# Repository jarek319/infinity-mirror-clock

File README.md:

# infinity-mirror-clock
An interesting visualization using the Infinity Mirror effect with a ring of RGB LEDs

I was playing with two-way acrylic and held it over a few Neopixels I had on hand, and found a really cool Infinity Mirror effect occuring when I angled the acrylic just right. Thinking about a good application for this, I decided to use to the effect to create "hands" for an analog-styled clock made of LEDs.

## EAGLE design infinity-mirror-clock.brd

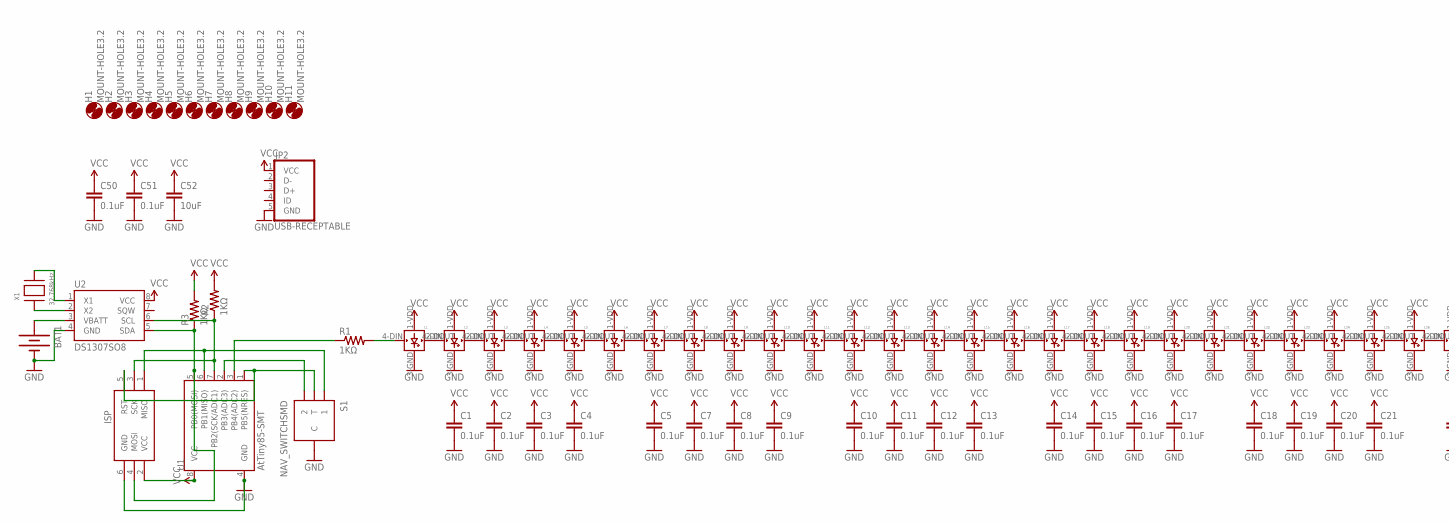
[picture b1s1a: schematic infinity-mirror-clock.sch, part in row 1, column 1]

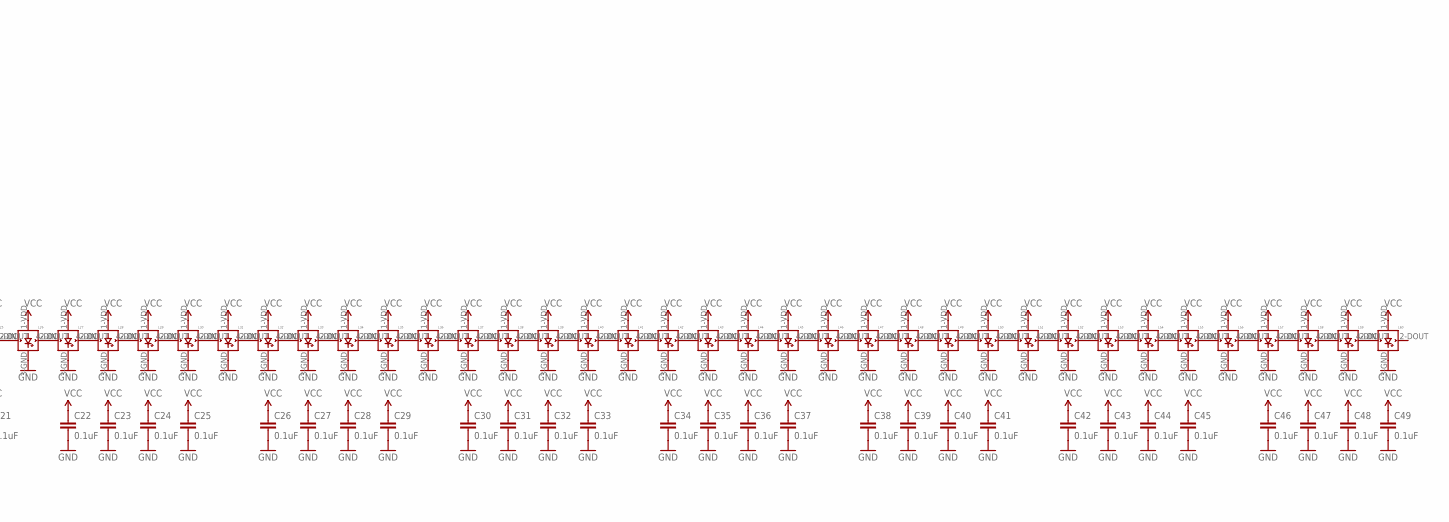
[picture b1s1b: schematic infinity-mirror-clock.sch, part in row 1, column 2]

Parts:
BAT1: BATTERY12MM; BATTCON_12MM
C1, C2, C3, C4, C5, C7, C8, C9, C10, C11, C12, C13, C14, C15, C16, C17, C18, C19, C20, C21, C22, C23, C24, C25, C26, C27, C28, C29, C30, C31, C32, C33, C34, C35, C36, C37, C38, C39, C40, C41, C42, C43, C44, C45, C46, C47, C48, C49, C50, C51: 0.1uF; 0603-CAP
C52: 10uF; 0603-CAP
H1, H2, H3, H4, H5, H6, H7, H8, H9, H10, H11: MOUNT-HOLE3.2; 3,2
ISP: AVRISPAVRSMTISP; AVRSMTISP
JP2: USB-RECEPTABLE; FCI-10103594-0001LF
L1, L2, L3, L4, L5, L6, L7, L8, L9, L10, L11, L12, L13, L14, L15, L16, L17, L18, L19, L20, L21, L22, L23, L24, L25, L26, L27, L28, L29, L30, L31, L32, L33, L34, L35, L36, L37, L38, L39, L40, L41, L42, L43, L44, L45, L46, L47, L48, L49, L50, L51, L52, L53, L54, L55, L56, L57, L58, L59, L60: WS2812B
R1: 1KΩ; 0603-RES
R2, R3: 1KΩ; R0603
S1: NAV_SWITCHSMD; NAV_SWITCH
U1: AtTiny85-SMT; SO08-EIAJ
U2: DS1307SO8; SO08
X1: 32.768kHz; XTAL3215

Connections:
GND: BAT1.GND (-), C1.2, C2.2, C3.2, C4.2, C5.2, C7.2, C8.2, C9.2, C10.2, C11.2, C12.2, C13.2, C14.2, C15.2, C16.2, C17.2, C18.2, C19.2, C20.2, C21.2, C22.2, C23.2, C24.2, C25.2, C26.2, C27.2, C28.2, C29.2, C30.2, C31.2, C32.2, C33.2, C34.2, C35.2, C36.2, C37.2, C38.2, C39.2, C40.2, C41.2, C42.2, C43.2, C44.2, C45.2, C46.2, C47.2, C48.2, C49.2, C50.2, C51.2, C52.2, ISP.6 (GND), JP2.5 (GND), L1.3-GND (GND), L2.3-GND (GND), L3.3-GND (GND), L4.3-GND (GND), L5.3-GND (GND), L6.3-GND (GND), L7.3-GND (GND), L8.3-GND (GND), L9.3-GND (GND), L10.3-GND (GND), L11.3-GND (GND), L12.3-GND (GND), L13.3-GND (GND), L14.3-GND (GND), L15.3-GND (GND), L16.3-GND (GND), L17.3-GND (GND), L18.3-GND (GND), L19.3-GND (GND), L20.3-GND (GND), L21.3-GND (GND), L22.3-GND (GND), L23.3-GND (GND), L24.3-GND (GND), L25.3-GND (GND), L26.3-GND (GND), L27.3-GND (GND), L28.3-GND (GND), L29.3-GND (GND), L30.3-GND (GND), L31.3-GND (GND), L32.3-GND (GND), L33.3-GND (GND), L34.3-GND (GND), L35.3-GND (GND), L36.3-GND (GND), L37.3-GND (GND), L38.3-GND (GND), L39.3-GND (GND), L40.3-GND (GND), L41.3-GND (GND), L42.3-GND (GND), L43.3-GND (GND), L44.3-GND (GND), L45.3-GND (GND), L46.3-GND (GND), L47.3-GND (GND), L48.3-GND (GND), L49.3-GND (GND), L50.3-GND (GND), L51.3-GND (GND), L52.3-GND (GND), L53.3-GND (GND), L54.3-GND (GND), L55.3-GND (GND), L56.3-GND (GND), L57.3-GND (GND), L58.3-GND (GND), L59.3-GND (GND), L60.3-GND (GND), S1.C, U1.4 (GND), U2.4 (GND)
unnamed: L1.2-DOUT (DOUT), L2.4-DIN (DIN)
unnamed: L2.2-DOUT (DOUT), L3.4-DIN (DIN)
unnamed: L3.2-DOUT (DOUT), L4.4-DIN (DIN)
unnamed: L4.2-DOUT (DOUT), L5.4-DIN (DIN)
unnamed: L5.2-DOUT (DOUT), L6.4-DIN (DIN)
unnamed: L7.2-DOUT (DOUT), L8.4-DIN (DIN)
unnamed: L8.2-DOUT (DOUT), L9.4-DIN (DIN)
unnamed: L9.2-DOUT (DOUT), L10.4-DIN (DIN)
unnamed: L10.2-DOUT (DOUT), L11.4-DIN (DIN)
unnamed: L11.2-DOUT (DOUT), L12.4-DIN (DIN)
unnamed: L13.2-DOUT (DOUT), L14.4-DIN (DIN)
unnamed: L14.2-DOUT (DOUT), L15.4-DIN (DIN)
unnamed: L15.2-DOUT (DOUT), L16.4-DIN (DIN)
unnamed: L16.2-DOUT (DOUT), L17.4-DIN (DIN)
unnamed: L17.2-DOUT (DOUT), L18.4-DIN (DIN)
unnamed: L19.2-DOUT (DOUT), L20.4-DIN (DIN)
unnamed: L20.2-DOUT (DOUT), L21.4-DIN (DIN)
unnamed: L21.2-DOUT (DOUT), L22.4-DIN (DIN)
unnamed: L22.2-DOUT (DOUT), L23.4-DIN (DIN)
unnamed: L23.2-DOUT (DOUT), L24.4-DIN (DIN)
unnamed: L25.2-DOUT (DOUT), L26.4-DIN (DIN)
unnamed: L26.2-DOUT (DOUT), L27.4-DIN (DIN)
unnamed: L27.2-DOUT (DOUT), L28.4-DIN (DIN)
unnamed: L28.2-DOUT (DOUT), L29.4-DIN (DIN)
unnamed: L29.2-DOUT (DOUT), L30.4-DIN (DIN)
unnamed: L31.2-DOUT (DOUT), L32.4-DIN (DIN)
unnamed: L32.2-DOUT (DOUT), L33.4-DIN (DIN)
unnamed: L33.2-DOUT (DOUT), L34.4-DIN (DIN)
unnamed: L34.2-DOUT (DOUT), L35.4-DIN (DIN)
unnamed: L35.2-DOUT (DOUT), L36.4-DIN (DIN)
unnamed: L37.2-DOUT (DOUT), L38.4-DIN (DIN)
unnamed: L38.2-DOUT (DOUT), L39.4-DIN (DIN)
unnamed: L39.2-DOUT (DOUT), L40.4-DIN (DIN)
unnamed: L40.2-DOUT (DOUT), L41.4-DIN (DIN)
unnamed: L41.2-DOUT (DOUT), L42.4-DIN (DIN)
unnamed: L43.2-DOUT (DOUT), L44.4-DIN (DIN)
unnamed: L44.2-DOUT (DOUT), L45.4-DIN (DIN)
unnamed: L45.2-DOUT (DOUT), L46.4-DIN (DIN)
unnamed: L46.2-DOUT (DOUT), L47.4-DIN (DIN)
unnamed: L47.2-DOUT (DOUT), L48.4-DIN (DIN)
unnamed: L49.2-DOUT (DOUT), L50.4-DIN (DIN)
unnamed: L50.2-DOUT (DOUT), L51.4-DIN (DIN)
unnamed: L51.2-DOUT (DOUT), L52.4-DIN (DIN)
unnamed: L52.2-DOUT (DOUT), L53.4-DIN (DIN)
unnamed: L53.2-DOUT (DOUT), L54.4-DIN (DIN)
unnamed: L55.2-DOUT (DOUT), L56.4-DIN (DIN)
unnamed: L56.2-DOUT (DOUT), L57.4-DIN (DIN)
unnamed: L57.2-DOUT (DOUT), L58.4-DIN (DIN)
unnamed: L58.2-DOUT (DOUT), L59.4-DIN (DIN)
unnamed: L59.2-DOUT (DOUT), L60.4-DIN (DIN)
unnamed: L1.4-DIN (DIN), R1.2
unnamed: U2.2 (X2), X1.P$1
unnamed: U2.1 (X1), X1.P$2
unnamed: BAT1.PWR@1 (+), U2.3 (VBATT)
unnamed: ISP.3 (SCK), R2.1, U1.7 (PB2(SCK/ADC1)), U2.6 (SCL)
unnamed: ISP.4 (MOSI), R3.1, U1.5 (PB0(MOSI)), U2.5 (SDA)
unnamed: ISP.1 (MISO), S1.1, U1.6 (PB1(MISO))
unnamed: S1.2, U1.2 (PB3(ADC3))
unnamed: ISP.5 (RST), S1.T, U1.1 (PB5(NRES))
unnamed: R1.1, U1.3 (PB4(ADC2))
unnamed: L30.2-DOUT (DOUT), L31.4-DIN (DIN)
unnamed: L24.2-DOUT (DOUT), L25.4-DIN (DIN)
unnamed: L18.2-DOUT (DOUT), L19.4-DIN (DIN)
unnamed: L12.2-DOUT (DOUT), L13.4-DIN (DIN)
unnamed: L36.2-DOUT (DOUT), L37.4-DIN (DIN)
unnamed: L42.2-DOUT (DOUT), L43.4-DIN (DIN)
unnamed: L48.2-DOUT (DOUT), L49.4-DIN (DIN)
unnamed: L54.2-DOUT (DOUT), L55.4-DIN (DIN)
unnamed: L6.2-DOUT (DOUT), L7.4-DIN (DIN)
VCC: C1.1, C2.1, C3.1, C4.1, C5.1, C7.1, C8.1, C9.1, C10.1, C11.1, C12.1, C13.1, C14.1, C15.1, C16.1, C17.1, C18.1, C19.1, C20.1, C21.1, C22.1, C23.1, C24.1, C25.1, C26.1, C27.1, C28.1, C29.1, C30.1, C31.1, C32.1, C33.1, C34.1, C35.1, C36.1, C37.1, C38.1, C39.1, C40.1, C41.1, C42.1, C43.1, C44.1, C45.1, C46.1, C47.1, C48.1, C49.1, C50.1, C51.1, C52.1, ISP.2 (VCC), JP2.1 (VCC), L1.1-VDD (VDD), L2.1-VDD (VDD), L3.1-VDD (VDD), L4.1-VDD (VDD), L5.1-VDD (VDD), L6.1-VDD (VDD), L7.1-VDD (VDD), L8.1-VDD (VDD), L9.1-VDD (VDD), L10.1-VDD (VDD), L11.1-VDD (VDD), L12.1-VDD (VDD), L13.1-VDD (VDD), L14.1-VDD (VDD), L15.1-VDD (VDD), L16.1-VDD (VDD), L17.1-VDD (VDD), L18.1-VDD (VDD), L19.1-VDD (VDD), L20.1-VDD (VDD), L21.1-VDD (VDD), L22.1-VDD (VDD), L23.1-VDD (VDD), L24.1-VDD (VDD), L25.1-VDD (VDD), L26.1-VDD (VDD), L27.1-VDD (VDD), L28.1-VDD (VDD), L29.1-VDD (VDD), L30.1-VDD (VDD), L31.1-VDD (VDD), L32.1-VDD (VDD), L33.1-VDD (VDD), L34.1-VDD (VDD), L35.1-VDD (VDD), L36.1-VDD (VDD), L37.1-VDD (VDD), L38.1-VDD (VDD), L39.1-VDD (VDD), L40.1-VDD (VDD), L41.1-VDD (VDD), L42.1-VDD (VDD), L43.1-VDD (VDD), L44.1-VDD (VDD), L45.1-VDD (VDD), L46.1-VDD (VDD), L47.1-VDD (VDD), L48.1-VDD (VDD), L49.1-VDD (VDD), L50.1-VDD (VDD), L51.1-VDD (VDD), L52.1-VDD (VDD), L53.1-VDD (VDD), L54.1-VDD (VDD), L55.1-VDD (VDD), L56.1-VDD (VDD), L57.1-VDD (VDD), L58.1-VDD (VDD), L59.1-VDD (VDD), L60.1-VDD (VDD), R2.2, R3.2, U1.8 (VCC), U2.8 (VCC)

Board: 4 copper layers, 132 parts (11 on the bottom side), 71 nets, no tracks yet.

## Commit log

2018-07-05 design tested: working
2018-07-05 added pictures

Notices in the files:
parts and their libraries:
SparkFun-Resistors: Licensing: CC v3.0 Share-Alike You are welcome to use this library for commercial purposes.
